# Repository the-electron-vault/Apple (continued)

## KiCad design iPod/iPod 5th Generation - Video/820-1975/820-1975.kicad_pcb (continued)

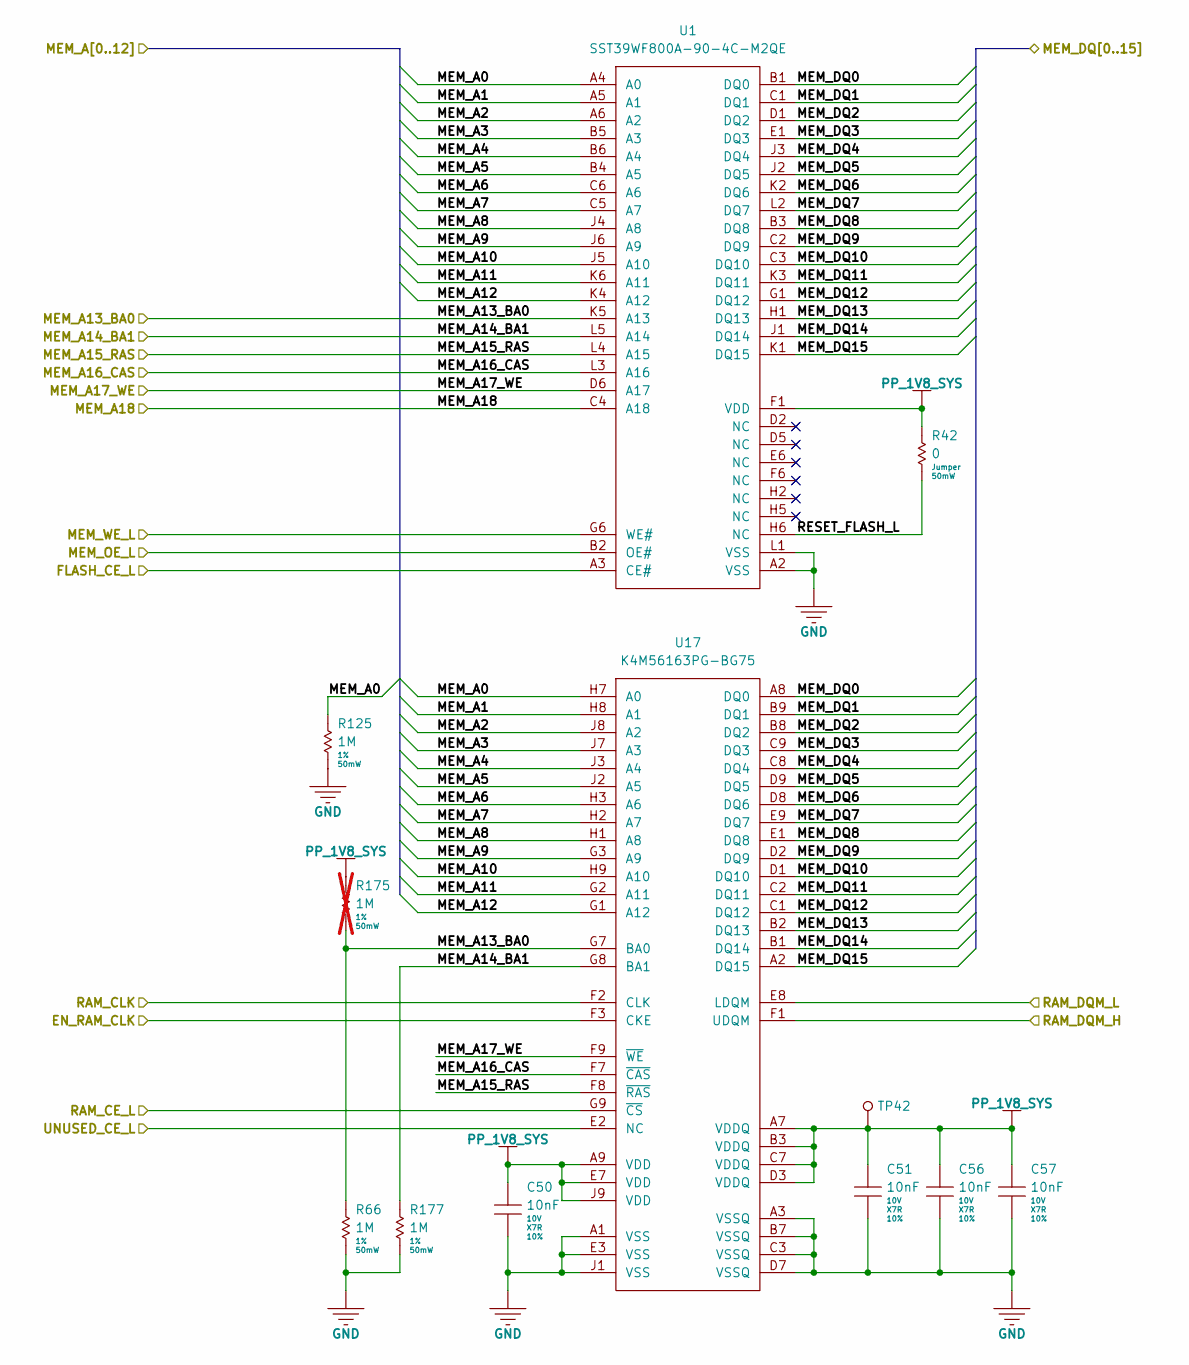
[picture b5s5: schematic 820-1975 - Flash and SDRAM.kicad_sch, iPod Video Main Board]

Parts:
C50, C51, C56, C57: 10nF; MLCC-0201; Voltage 10V; Tolerance 10%; Manufacturer Part Number GRM033R71A103KA01D
R42: 0; RES-0201; Tolerance Jumper; Manufacturer Part Number CRCW02010000Z0ED
R66, R125, R177: 1M; RES-0201; Tolerance 1%; Manufacturer Part Number CRCW02011M00FNED
R175: 1M; RES-0201; Tolerance 1%; Manufacturer Part Number CRCW02011M00FNED; not fitted
TP42: TP; TP-SMT
U1: SST39WF800A-90-4C-M2QE; Manufacturer Part Number SST39WF800A-90-4C-M2QE
U17: K4M56163PG-BG75; K4M56163PG; Manufacturer Part Number K4M56163PG-BG75

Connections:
/Flash-and-SDRAM/EN_RAM_CLK: U17.F3 (CKE); also elsewhere on the board
/Flash-and-SDRAM/FLASH_CE_L: U1.A3 (CE#); also elsewhere on the board
/Flash-and-SDRAM/MEM_A0: R125.1, U1.A4 (A0), U17.H7 (A0); also elsewhere on the board
/Flash-and-SDRAM/MEM_A1: U1.A5 (A1), U17.H8 (A1); also elsewhere on the board
/Flash-and-SDRAM/MEM_A2: U1.A6 (A2), U17.J8 (A2); also elsewhere on the board
/Flash-and-SDRAM/MEM_A3: U1.B5 (A3), U17.J7 (A3); also elsewhere on the board
/Flash-and-SDRAM/MEM_A4: U1.B6 (A4), U17.J3 (A4); also elsewhere on the board
/Flash-and-SDRAM/MEM_A5: U1.B4 (A5), U17.J2 (A5); also elsewhere on the board
/Flash-and-SDRAM/MEM_A6: U1.C6 (A6), U17.H3 (A6); also elsewhere on the board
/Flash-and-SDRAM/MEM_A7: U1.C5 (A7), U17.H2 (A7); also elsewhere on the board
/Flash-and-SDRAM/MEM_A8: U1.J4 (A8), U17.H1 (A8); also elsewhere on the board
/Flash-and-SDRAM/MEM_A9: U1.J6 (A9), U17.G3 (A9); also elsewhere on the board
/Flash-and-SDRAM/MEM_A10: U1.J5 (A10), U17.H9 (A10); also elsewhere on the board
/Flash-and-SDRAM/MEM_A11: U1.K6 (A11), U17.G2 (A11); also elsewhere on the board
/Flash-and-SDRAM/MEM_A12: U1.K4 (A12), U17.G1 (A12); also elsewhere on the board
/Flash-and-SDRAM/MEM_A13_BA0: R66.1, R175.2, U1.K5 (A13), U17.G7 (BA0); also elsewhere on the board
/Flash-and-SDRAM/MEM_A14_BA1: R177.1, U1.L5 (A14), U17.G8 (BA1); also elsewhere on the board
/Flash-and-SDRAM/MEM_A15_RAS: U1.L4 (A15), U17.F8 (~RAS); also elsewhere on the board
/Flash-and-SDRAM/MEM_A16_CAS: U1.L3 (A16), U17.F7 (~CAS); also elsewhere on the board
/Flash-and-SDRAM/MEM_A17_WE: U1.D6 (A17), U17.F9 (~WE); also elsewhere on the board
/Flash-and-SDRAM/MEM_A18: U1.C4 (A18); also elsewhere on the board
/Flash-and-SDRAM/MEM_DQ0: U1.B1 (DQ0), U17.A8 (DQ0); also elsewhere on the board
/Flash-and-SDRAM/MEM_DQ1: U1.C1 (DQ1), U17.B9 (DQ1); also elsewhere on the board
/Flash-and-SDRAM/MEM_DQ2: U1.D1 (DQ2), U17.B8 (DQ2); also elsewhere on the board
/Flash-and-SDRAM/MEM_DQ3: U1.E1 (DQ3), U17.C9 (DQ3); also elsewhere on the board
/Flash-and-SDRAM/MEM_DQ4: U1.J3 (DQ4), U17.C8 (DQ4); also elsewhere on the board
/Flash-and-SDRAM/MEM_DQ5: U1.J2 (DQ5), U17.D9 (DQ5); also elsewhere on the board
/Flash-and-SDRAM/MEM_DQ6: U1.K2 (DQ6), U17.D8 (DQ6); also elsewhere on the board
/Flash-and-SDRAM/MEM_DQ7: U1.L2 (DQ7), U17.E9 (DQ7); also elsewhere on the board
/Flash-and-SDRAM/MEM_DQ8: U1.B3 (DQ8), U17.E1 (DQ8); also elsewhere on the board
/Flash-and-SDRAM/MEM_DQ9: U1.C2 (DQ9), U17.D2 (DQ9); also elsewhere on the board
/Flash-and-SDRAM/MEM_DQ10: U1.C3 (DQ10), U17.D1 (DQ10); also elsewhere on the board
/Flash-and-SDRAM/MEM_DQ11: U1.K3 (DQ11), U17.C2 (DQ11); also elsewhere on the board
/Flash-and-SDRAM/MEM_DQ12: U1.G1 (DQ12), U17.C1 (DQ12); also elsewhere on the board
/Flash-and-SDRAM/MEM_DQ13: U1.H1 (DQ13), U17.B2 (DQ13); also elsewhere on the board
/Flash-and-SDRAM/MEM_DQ14: U1.J1 (DQ14), U17.B1 (DQ14); also elsewhere on the board
/Flash-and-SDRAM/MEM_DQ15: U1.K1 (DQ15), U17.A2 (DQ15); also elsewhere on the board
/Flash-and-SDRAM/MEM_OE_L: U1.B2 (OE#); also elsewhere on the board
/Flash-and-SDRAM/MEM_WE_L: U1.G6 (WE#); also elsewhere on the board
/Flash-and-SDRAM/RAM_CE_L: U17.G9 (~CS); also elsewhere on the board
/Flash-and-SDRAM/RAM_CLK: U17.F2 (CLK); also elsewhere on the board
/Flash-and-SDRAM/RAM_DQM_H: U17.F1 (UDQM); also elsewhere on the board
/Flash-and-SDRAM/RAM_DQM_L: U17.E8 (LDQM); also elsewhere on the board
/Flash-and-SDRAM/RESET_FLASH_L: R42.2, U1.H6 (NC)
/Flash-and-SDRAM/UNUSED_CE_L: U17.E2 (NC); also elsewhere on the board
GND: C50.2, C51.2, C56.2, C57.2, R66.2, R125.2, R177.2, U1.A2 (VSS), U1.L1 (VSS), U17.A1 (VSS), U17.A3 (VSSQ), U17.B7 (VSSQ), U17.C3 (VSSQ), U17.D7 (VSSQ), U17.E3 (VSS), U17.J1 (VSS); also elsewhere on the board
PP_1V8_SYS: C50.1, C51.1, C56.1, C57.1, R42.1, R175.1, TP42.1, U1.F1 (VDD), U17.A7 (VDDQ), U17.A9 (VDD), U17.B3 (VDDQ), U17.C7 (VDDQ), U17.D3 (VDDQ), U17.E7 (VDD), U17.J9 (VDD); also elsewhere on the board

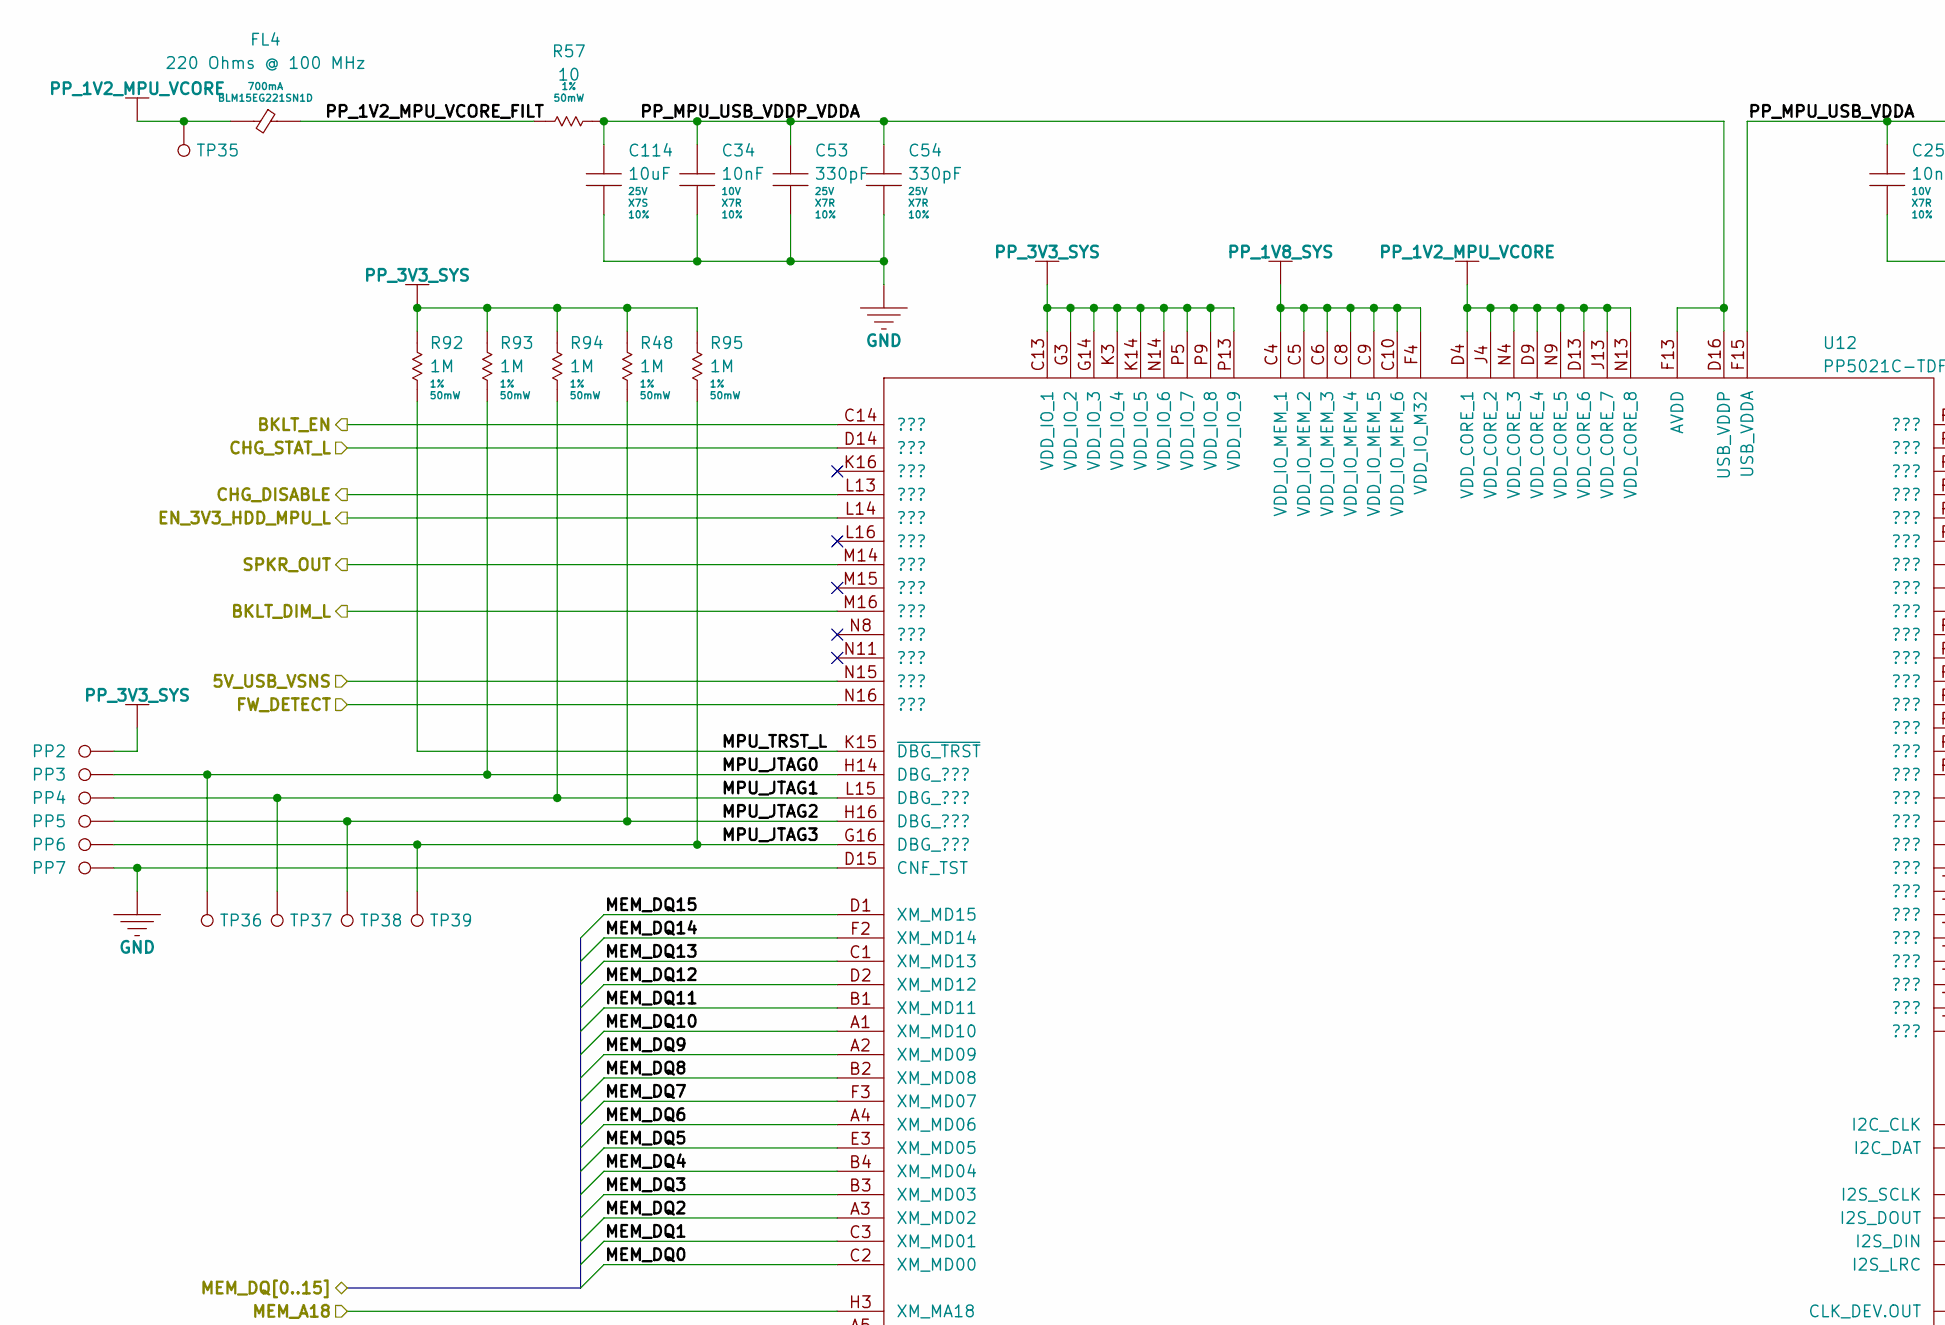
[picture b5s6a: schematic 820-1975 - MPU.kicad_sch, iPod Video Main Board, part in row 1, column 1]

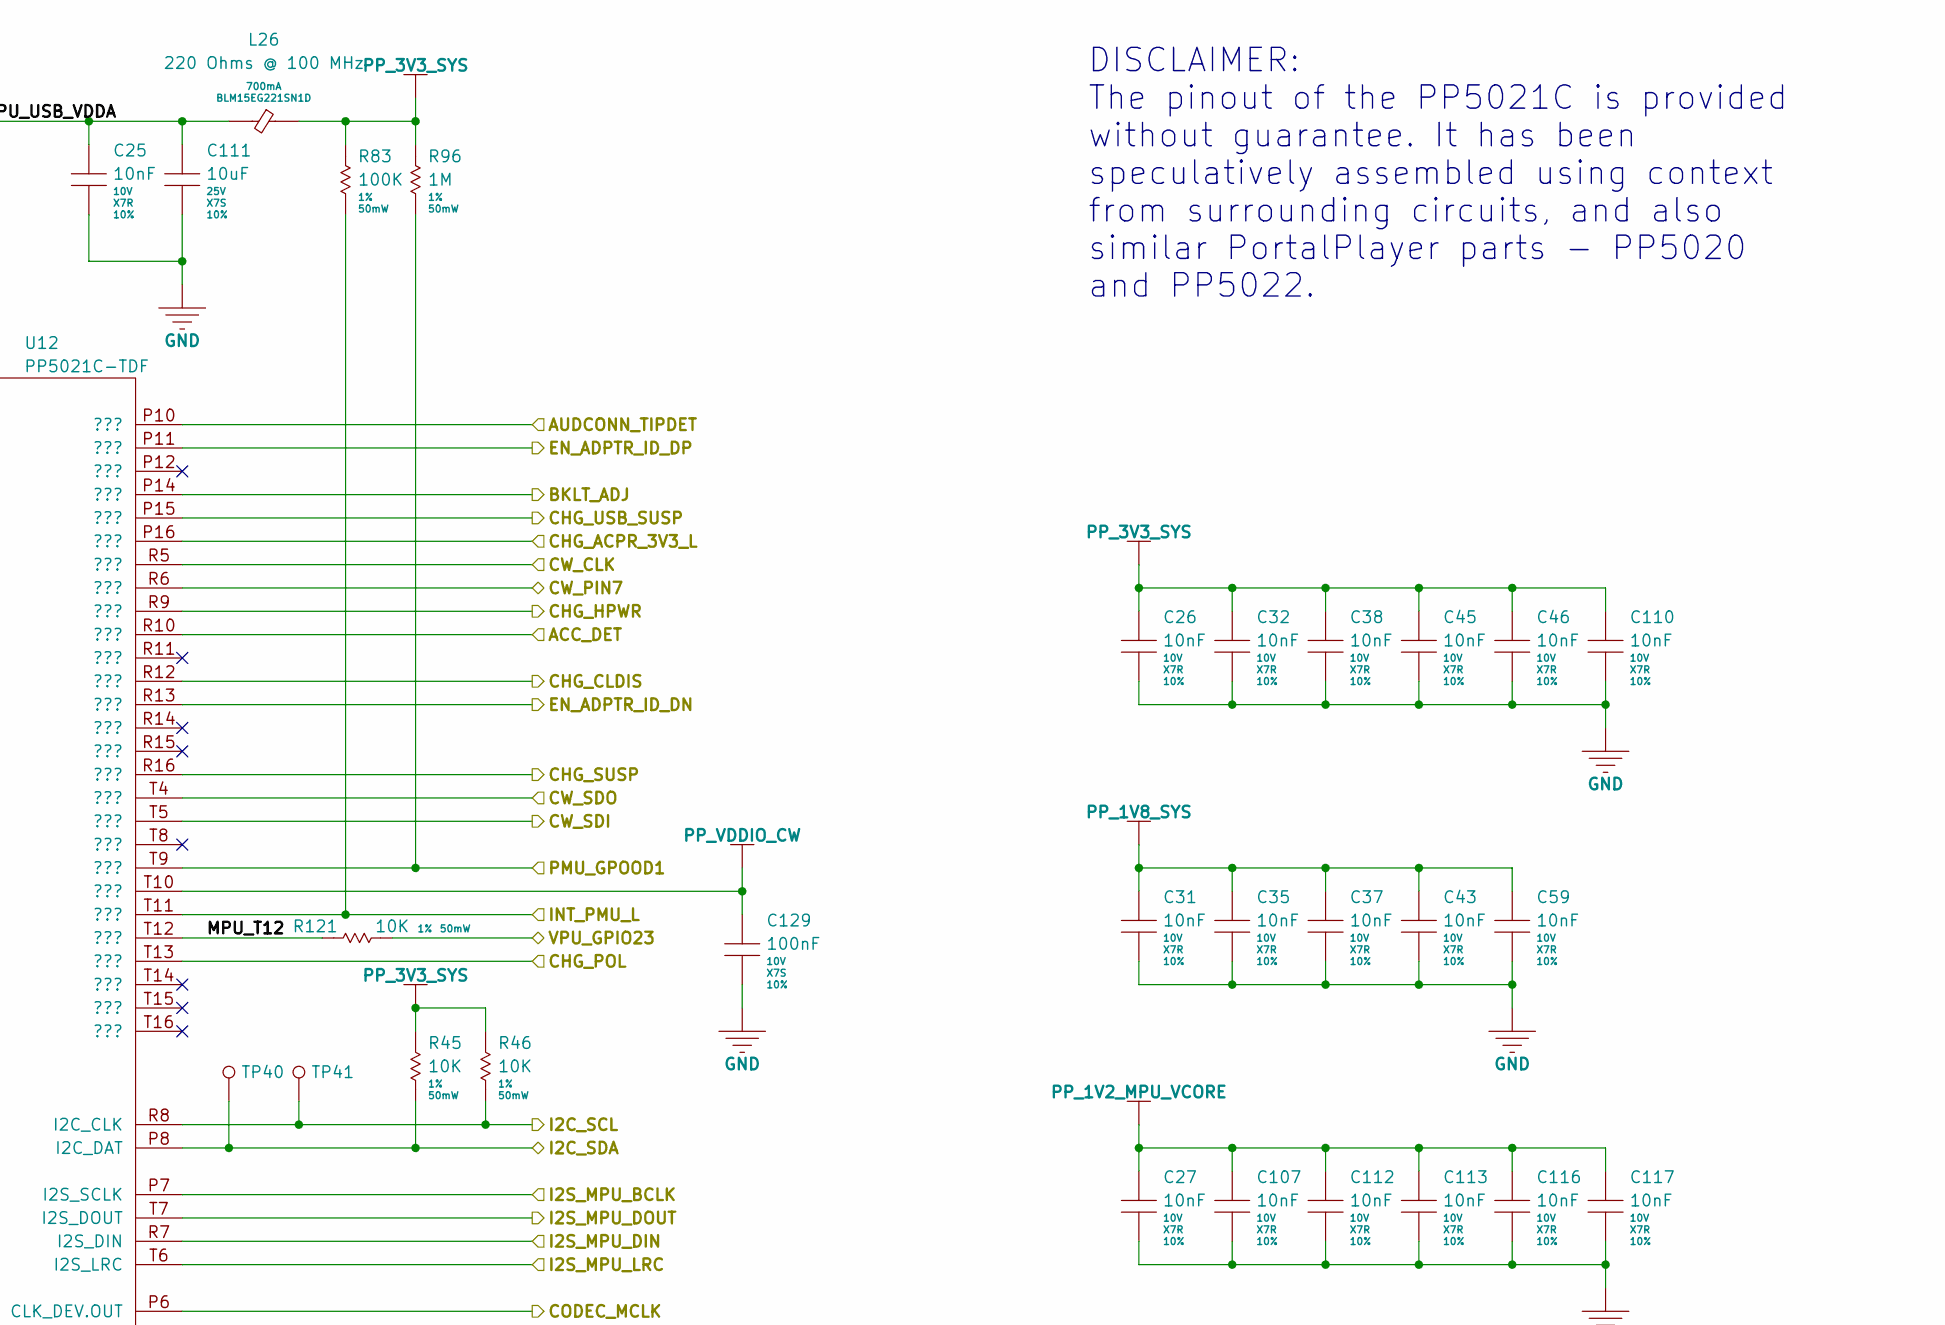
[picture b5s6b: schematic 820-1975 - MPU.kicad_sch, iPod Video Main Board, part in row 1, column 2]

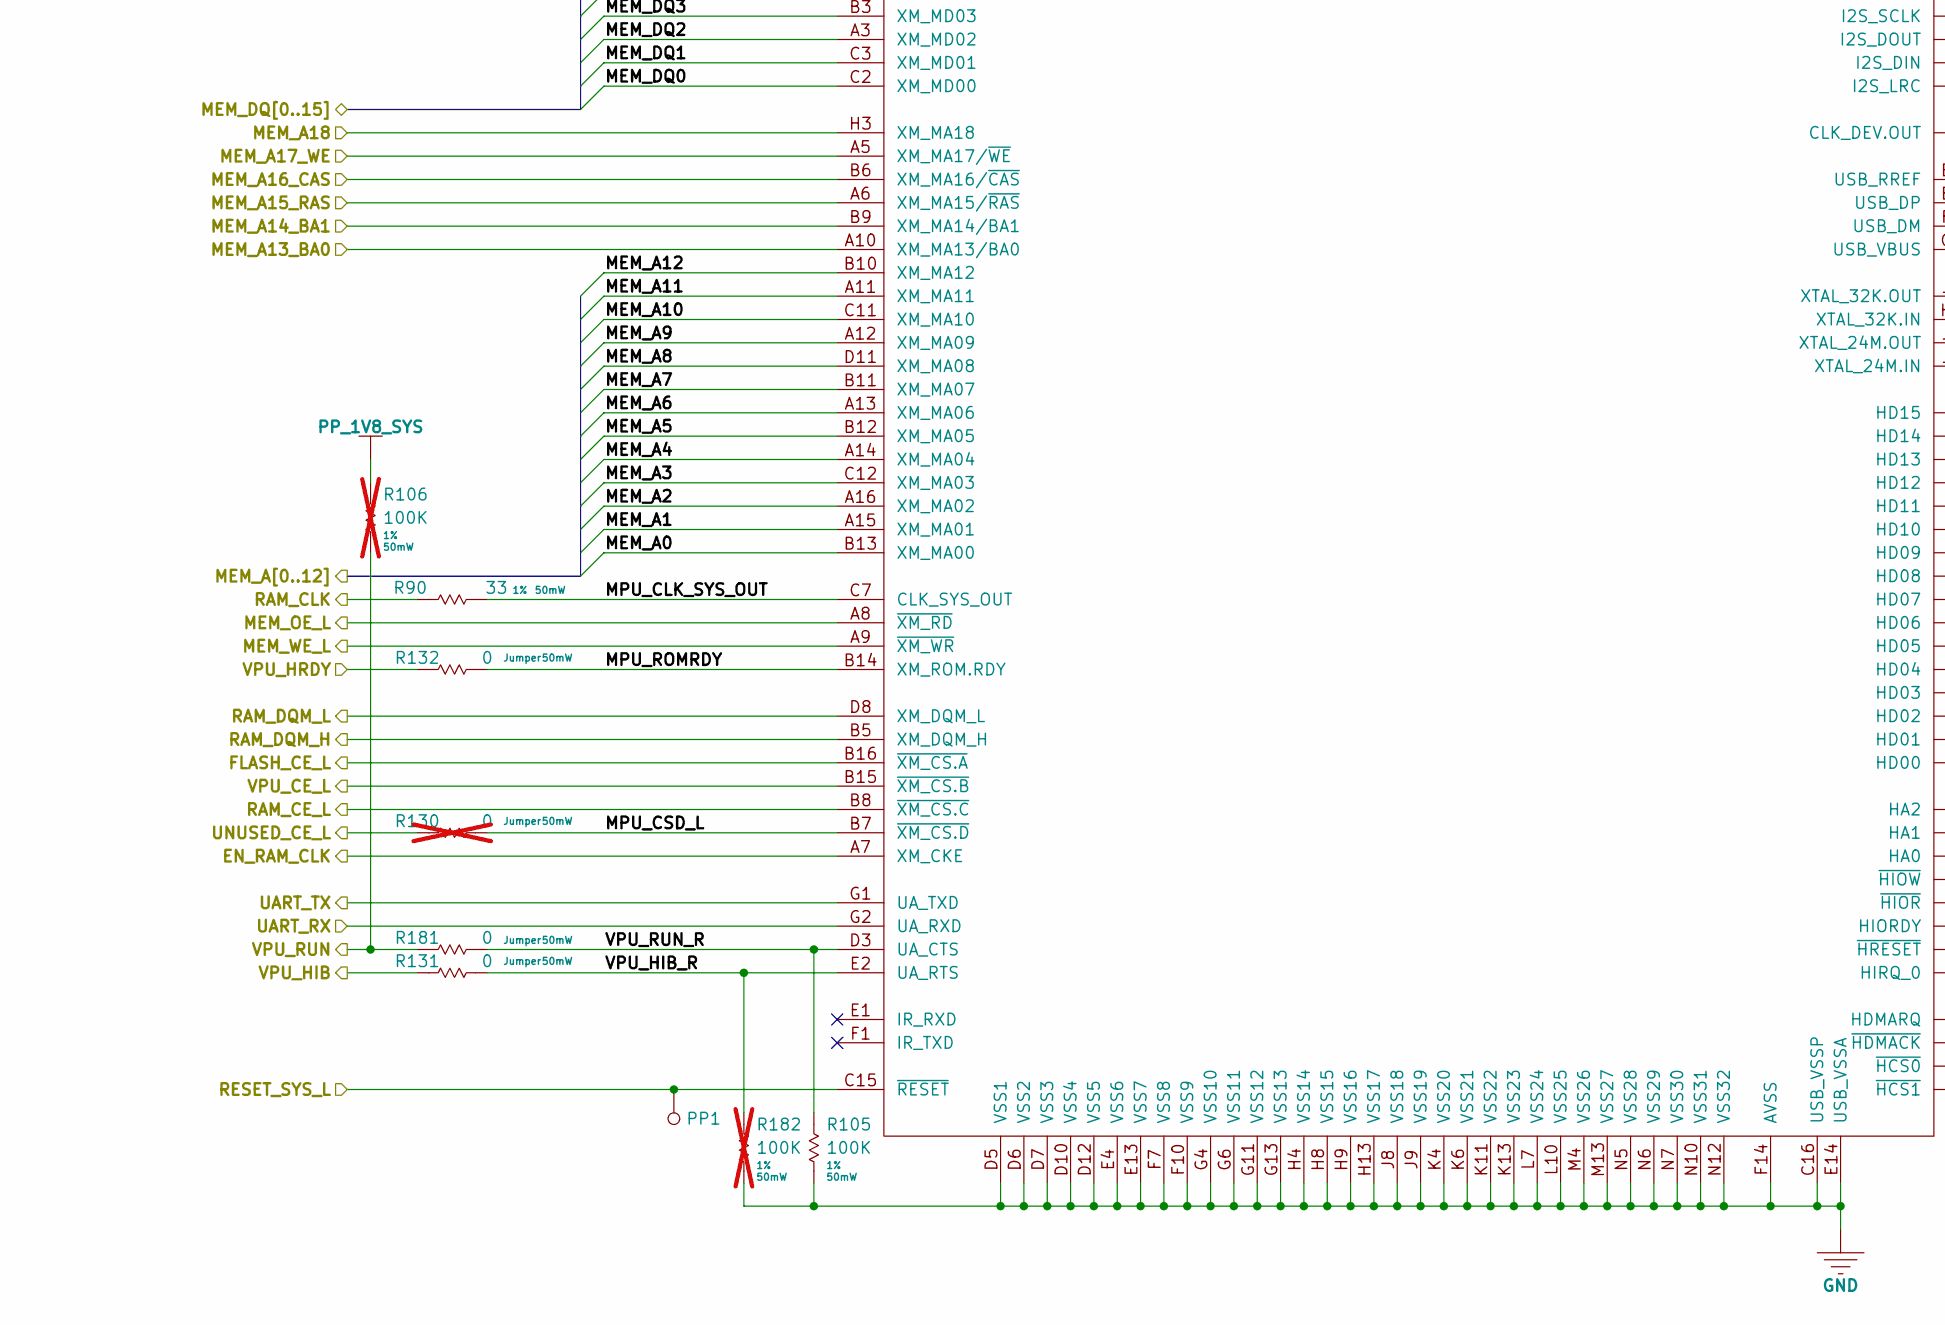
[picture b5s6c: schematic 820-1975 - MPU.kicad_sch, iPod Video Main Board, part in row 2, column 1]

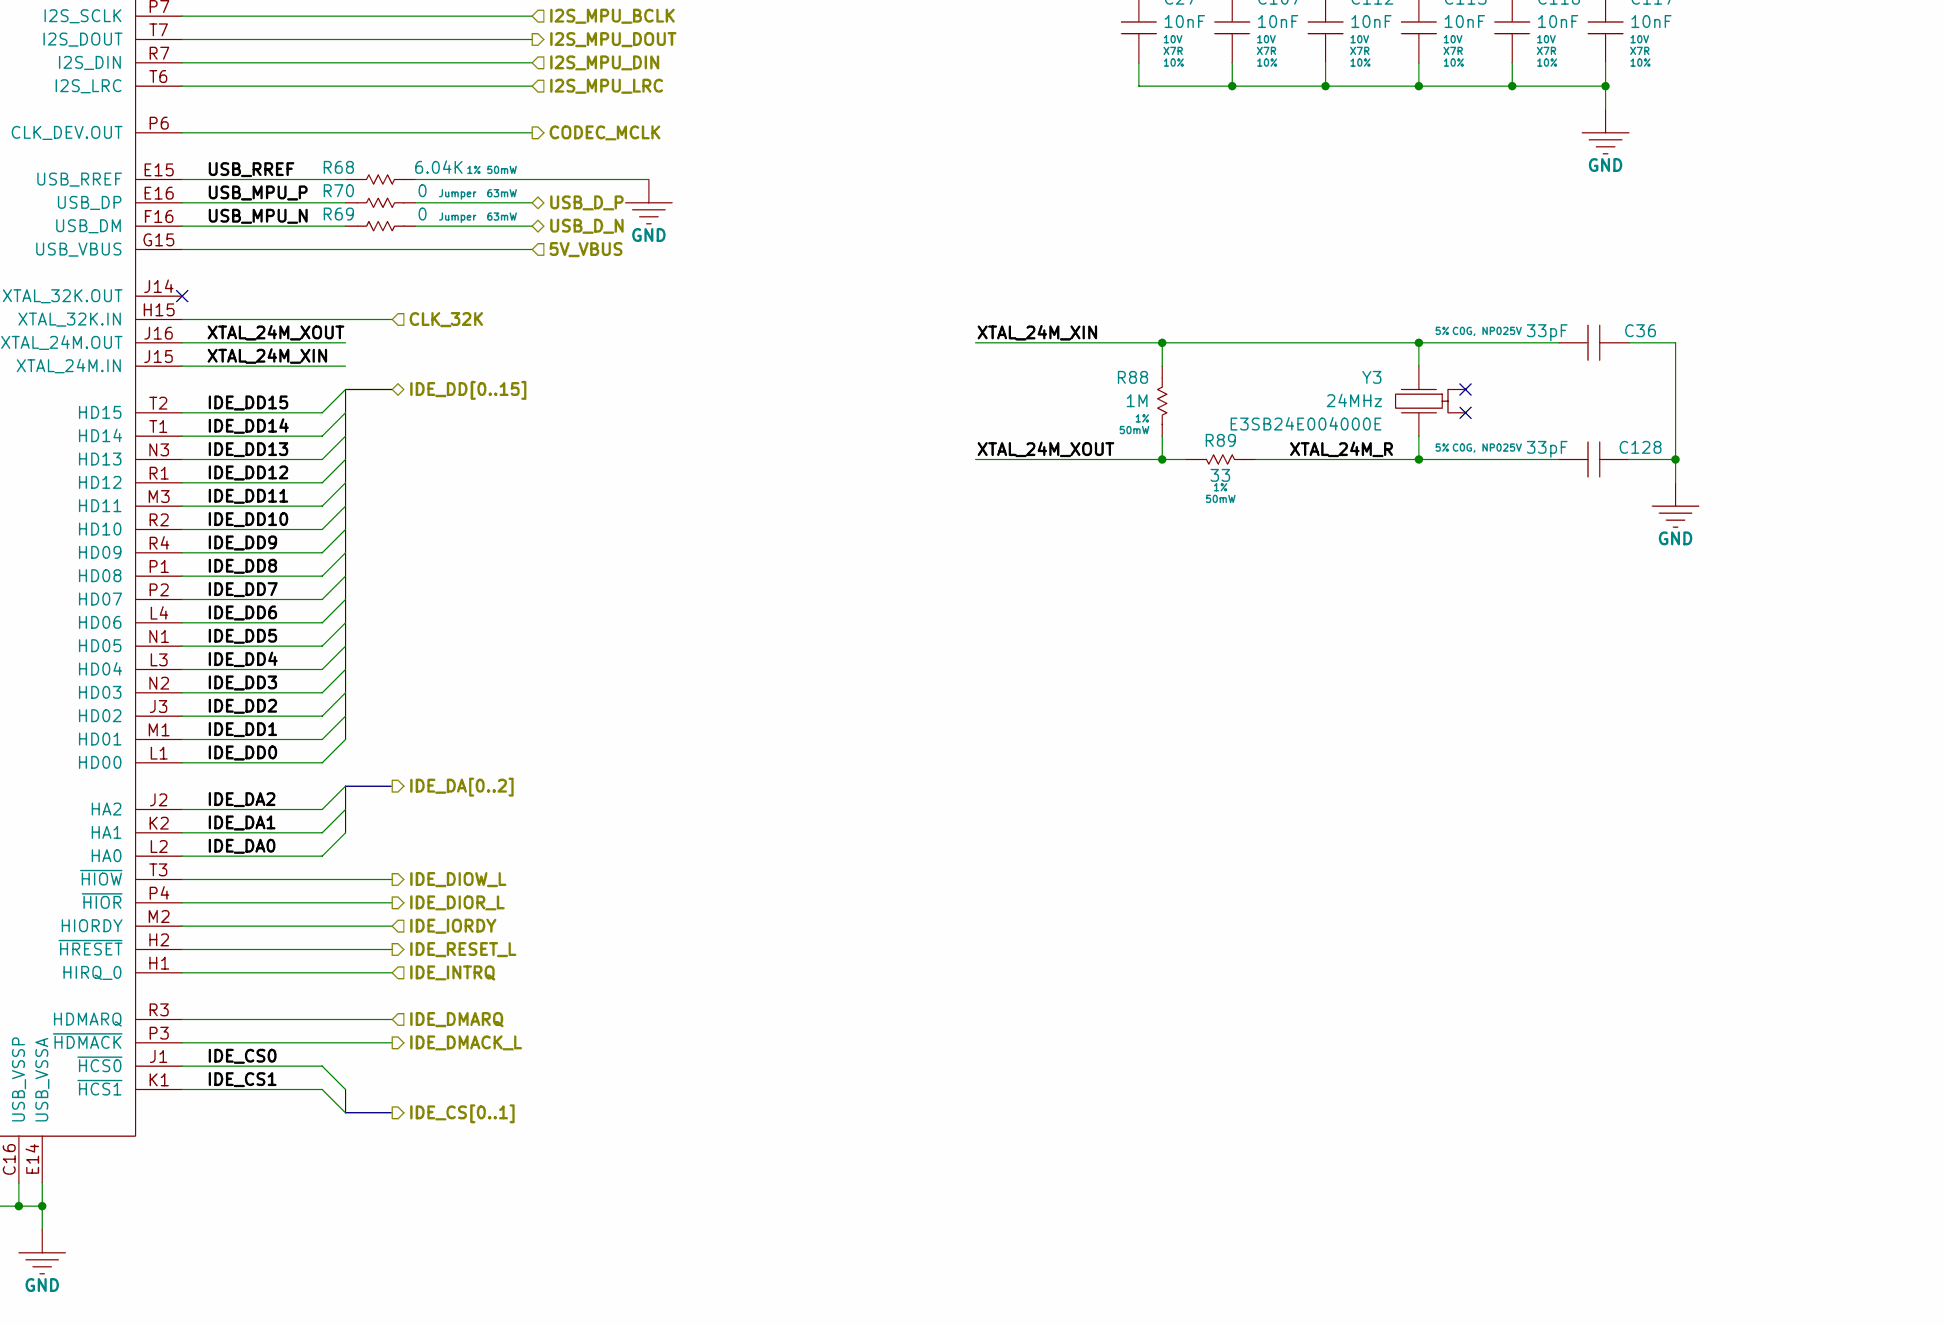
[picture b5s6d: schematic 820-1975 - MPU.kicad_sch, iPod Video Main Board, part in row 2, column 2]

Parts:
C25, C26, C27, C31, C32, C34, C35, C37, C38, C43, C45, C46, C59, C107, C110, C112, C113, C116, C117: 10nF; MLCC-0201; Voltage 10V; Tolerance 10%; Manufacturer Part Number GRM033R71A103KA01D
C36, C128: 33pF; MLCC-0201; Voltage 25V; Tolerance 5%; Manufacturer Part Number GRM0335C1E330JA01D
C53, C54: 330pF; MLCC-0201; Voltage 25V; Tolerance 10%; Manufacturer Part Number GRM033R71E331KA01D
C111, C114: 10uF; MLCC-0805; Voltage 25V; Tolerance 10%; Manufacturer Part Number GRM21BC71E106KE11L
C129: 100nF; MLCC-0201; Voltage 10V; Tolerance 10%; Manufacturer Part Number GRM033C71A104KE14D
FL4: 220 Ohms @ 100 MHz; FB-0402; Manufacturer Part Number BLM15EG221SN1D
L26: 220 Ohms @ 100 MHz; FB-0402; Manufacturer Part Number BLM15EG221SN1D
PP1, PP2, PP3, PP4, PP5, PP6, PP7: TP; TP-SMT
R45, R46, R121: 10K; RES-0201; Tolerance 1%; Manufacturer Part Number CRCW020110K0FNED
R48, R88, R92, R93, R94, R95, R96: 1M; RES-0201; Tolerance 1%; Manufacturer Part Number CRCW02011M00FNED
R57: 10; RES-0201; Tolerance 1%; Manufacturer Part Number CRCW020110R0FNED
R68: 6.04K; RES-0201; Tolerance 1%; Manufacturer Part Number CRCW02016K04FNED
R69, R70: 0; RES-0402; Tolerance Jumper; Manufacturer Part Number CRCW04020000Z0ED
R83, R105: 100K; RES-0201; Tolerance 1%; Manufacturer Part Number CRCW0201100KFNED
R89, R90: 33; RES-0201; Tolerance 1%; Manufacturer Part Number CRCW020133R0FNED
R106, R182: 100K; RES-0201; Tolerance 1%; Manufacturer Part Number CRCW0201100KFNED; not fitted
R130: 0; RES-0201; Tolerance Jumper; Manufacturer Part Number CRCW02010000Z0ED; not fitted
R131, R132, R181: 0; RES-0201; Tolerance Jumper; Manufacturer Part Number CRCW02010000Z0ED
TP35, TP36, TP37, TP38, TP39, TP40, TP41: TP; TP-SMT
U12: PP5021C-TDF; Manufacturer Part Number PP5021C-TDF
Y3: 24MHz; XTAL-3.2x2.5; Tolerance 10ppm; Manufacturer Part Number E3SB24E004000E

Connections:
/BKLT_ADJ: U12.P14 (???); also elsewhere on the board
/BKLT_DIM_L: U12.M16 (???); also elsewhere on the board
/BKLT_EN: U12.C14 (???); also elsewhere on the board
/CODEC/AUDCONN_TIPDET: U12.P10 (???); also elsewhere on the board
/CODEC/CODEC_MCLK: U12.P6 (CLK_DEV.OUT); also elsewhere on the board
/CODEC/I2C_SCL: R46.2, TP41.1, U12.R8 (I2C_CLK); also elsewhere on the board
/CODEC/I2C_SDA: R45.2, TP40.1, U12.P8 (I2C_DAT); also elsewhere on the board
/CODEC/I2S_MPU_BCLK: U12.P7 (I2S_SCLK); also elsewhere on the board
/CODEC/I2S_MPU_DIN: U12.R7 (I2S_DIN); also elsewhere on the board
/CODEC/I2S_MPU_DOUT: U12.T7 (I2S_DOUT); also elsewhere on the board
/CODEC/I2S_MPU_LRC: U12.T6 (I2S_LRC); also elsewhere on the board
/CODEC/SPKR_OUT: U12.M14 (???); also elsewhere on the board
/Charger-and-3.3V-Supply/CHG_ACPR_3V3_L: U12.P16 (???); also elsewhere on the board
/Charger-and-3.3V-Supply/CHG_CLDIS: U12.R12 (???); also elsewhere on the board
/Charger-and-3.3V-Supply/CHG_DISABLE: U12.L13 (???); also elsewhere on the board
/Charger-and-3.3V-Supply/CHG_HPWR: U12.R9 (???); also elsewhere on the board
/Charger-and-3.3V-Supply/CHG_POL: U12.T13 (???); also elsewhere on the board
/Charger-and-3.3V-Supply/CHG_STAT_L: U12.D14 (???); also elsewhere on the board
/Charger-and-3.3V-Supply/CHG_SUSP: U12.R16 (???); also elsewhere on the board
/Charger-and-3.3V-Supply/CHG_USB_SUSP: U12.P15 (???); also elsewhere on the board
/Click-Wheel/CW_CLK: U12.R5 (???); also elsewhere on the board
/Click-Wheel/CW_PIN7: U12.R6 (???); also elsewhere on the board
/Click-Wheel/CW_SDI: U12.T5 (???); also elsewhere on the board
/Click-Wheel/CW_SDO: U12.T4 (???); also elsewhere on the board
/Dock-Interface/5V_USB_VSNS: U12.N15 (???); also elsewhere on the board
/Dock-Interface/5V_VBUS: U12.G15 (USB_VBUS); also elsewhere on the board
/Dock-Interface/EN_ADPTR_ID_DN: U12.R13 (???); also elsewhere on the board
/Dock-Interface/EN_ADPTR_ID_DP: U12.P11 (???); also elsewhere on the board
/Dock-Interface/FW_DETECT: U12.N16 (???); also elsewhere on the board
/Dock-Interface/UART_RX: U12.G2 (UA_RXD); also elsewhere on the board
/Dock-Interface/UART_TX: U12.G1 (UA_TXD); also elsewhere on the board
/Dock-Interface/USB_D_N: R69.2; also elsewhere on the board
/Dock-Interface/USB_D_P: R70.2; also elsewhere on the board
/Flash-and-SDRAM/EN_RAM_CLK: U12.A7 (XM_CKE); also elsewhere on the board
/Flash-and-SDRAM/FLASH_CE_L: U12.B16 (~XM_CS.A); also elsewhere on the board
/Flash-and-SDRAM/MEM_A0: U12.B13 (XM_MA00); also elsewhere on the board
/Flash-and-SDRAM/MEM_A1: U12.A15 (XM_MA01); also elsewhere on the board
/Flash-and-SDRAM/MEM_A2: U12.A16 (XM_MA02); also elsewhere on the board
/Flash-and-SDRAM/MEM_A3: U12.C12 (XM_MA03); also elsewhere on the board
/Flash-and-SDRAM/MEM_A4: U12.A14 (XM_MA04); also elsewhere on the board
/Flash-and-SDRAM/MEM_A5: U12.B12 (XM_MA05); also elsewhere on the board
/Flash-and-SDRAM/MEM_A6: U12.A13 (XM_MA06); also elsewhere on the board
/Flash-and-SDRAM/MEM_A7: U12.B11 (XM_MA07); also elsewhere on the board
/Flash-and-SDRAM/MEM_A8: U12.D11 (XM_MA08); also elsewhere on the board
/Flash-and-SDRAM/MEM_A9: U12.A12 (XM_MA09); also elsewhere on the board
/Flash-and-SDRAM/MEM_A10: U12.C11 (XM_MA10); also elsewhere on the board
/Flash-and-SDRAM/MEM_A11: U12.A11 (XM_MA11); also elsewhere on the board
/Flash-and-SDRAM/MEM_A12: U12.B10 (XM_MA12); also elsewhere on the board
/Flash-and-SDRAM/MEM_A13_BA0: U12.A10 (XM_MA13/BA0); also elsewhere on the board
/Flash-and-SDRAM/MEM_A14_BA1: U12.B9 (XM_MA14/BA1); also elsewhere on the board
/Flash-and-SDRAM/MEM_A15_RAS: U12.A6 (XM_MA15/~RAS); also elsewhere on the board
/Flash-and-SDRAM/MEM_A16_CAS: U12.B6 (XM_MA16/~CAS); also elsewhere on the board
/Flash-and-SDRAM/MEM_A17_WE: U12.A5 (XM_MA17/~WE); also elsewhere on the board
/Flash-and-SDRAM/MEM_A18: U12.H3 (XM_MA18); also elsewhere on the board
/Flash-and-SDRAM/MEM_DQ0: U12.C2 (XM_MD00); also elsewhere on the board
/Flash-and-SDRAM/MEM_DQ1: U12.C3 (XM_MD01); also elsewhere on the board
/Flash-and-SDRAM/MEM_DQ2: U12.A3 (XM_MD02); also elsewhere on the board
/Flash-and-SDRAM/MEM_DQ3: U12.B3 (XM_MD03); also elsewhere on the board
/Flash-and-SDRAM/MEM_DQ4: U12.B4 (XM_MD04); also elsewhere on the board
/Flash-and-SDRAM/MEM_DQ5: U12.E3 (XM_MD05); also elsewhere on the board
/Flash-and-SDRAM/MEM_DQ6: U12.A4 (XM_MD06); also elsewhere on the board
/Flash-and-SDRAM/MEM_DQ7: U12.F3 (XM_MD07); also elsewhere on the board
/Flash-and-SDRAM/MEM_DQ8: U12.B2 (XM_MD08); also elsewhere on the board
/Flash-and-SDRAM/MEM_DQ9: U12.A2 (XM_MD09); also elsewhere on the board
/Flash-and-SDRAM/MEM_DQ10: U12.A1 (XM_MD10); also elsewhere on the board
/Flash-and-SDRAM/MEM_DQ11: U12.B1 (XM_MD11); also elsewhere on the board
/Flash-and-SDRAM/MEM_DQ12: U12.D2 (XM_MD12); also elsewhere on the board
/Flash-and-SDRAM/MEM_DQ13: U12.C1 (XM_MD13); also elsewhere on the board
/Flash-and-SDRAM/MEM_DQ14: U12.F2 (XM_MD14); also elsewhere on the board
/Flash-and-SDRAM/MEM_DQ15: U12.D1 (XM_MD15); also elsewhere on the board
/Flash-and-SDRAM/MEM_OE_L: U12.A8 (~XM_RD); also elsewhere on the board
/Flash-and-SDRAM/MEM_WE_L: U12.A9 (~XM_WR); also elsewhere on the board
/Flash-and-SDRAM/RAM_CE_L: U12.B8 (~XM_CS.C); also elsewhere on the board
/Flash-and-SDRAM/RAM_CLK: R90.1; also elsewhere on the board
/Flash-and-SDRAM/RAM_DQM_H: U12.B5 (XM_DQM_H); also elsewhere on the board
/Flash-and-SDRAM/RAM_DQM_L: U12.D8 (XM_DQM_L); also elsewhere on the board
/Flash-and-SDRAM/UNUSED_CE_L: R130.1; also elsewhere on the board
/Hard-Disk/EN_3V3_HDD_MPU_L: U12.L14 (???); also elsewhere on the board
/Hard-Disk/IDE_CS0: U12.J1 (~HCS0); also elsewhere on the board
/Hard-Disk/IDE_CS1: U12.K1 (~HCS1); also elsewhere on the board
/Hard-Disk/IDE_DA0: U12.L2 (HA0); also elsewhere on the board
/Hard-Disk/IDE_DA1: U12.K2 (HA1); also elsewhere on the board
/Hard-Disk/IDE_DA2: U12.J2 (HA2); also elsewhere on the board
/Hard-Disk/IDE_DD0: U12.L1 (HD00); also elsewhere on the board
/Hard-Disk/IDE_DD1: U12.M1 (HD01); also elsewhere on the board
/Hard-Disk/IDE_DD2: U12.J3 (HD02); also elsewhere on the board
/Hard-Disk/IDE_DD3: U12.N2 (HD03); also elsewhere on the board
/Hard-Disk/IDE_DD4: U12.L3 (HD04); also elsewhere on the board
/Hard-Disk/IDE_DD5: U12.N1 (HD05); also elsewhere on the board
/Hard-Disk/IDE_DD6: U12.L4 (HD06); also elsewhere on the board
/Hard-Disk/IDE_DD7: U12.P2 (HD07); also elsewhere on the board
/Hard-Disk/IDE_DD8: U12.P1 (HD08); also elsewhere on the board
/Hard-Disk/IDE_DD9: U12.R4 (HD09); also elsewhere on the board
/Hard-Disk/IDE_DD10: U12.R2 (HD10); also elsewhere on the board
/Hard-Disk/IDE_DD11: U12.M3 (HD11); also elsewhere on the board
/Hard-Disk/IDE_DD12: U12.R1 (HD12); also elsewhere on the board
/Hard-Disk/IDE_DD13: U12.N3 (HD13); also elsewhere on the board
/Hard-Disk/IDE_DD14: U12.T1 (HD14); also elsewhere on the board
/Hard-Disk/IDE_DD15: U12.T2 (HD15); also elsewhere on the board
/Hard-Disk/IDE_DIOR_L: U12.P4 (~HIOR); also elsewhere on the board
/Hard-Disk/IDE_DIOW_L: U12.T3 (~HIOW); also elsewhere on the board
/Hard-Disk/IDE_DMACK_L: U12.P3 (~HDMACK); also elsewhere on the board
/Hard-Disk/IDE_DMARQ: U12.R3 (HDMARQ); also elsewhere on the board
/Hard-Disk/IDE_INTRQ: U12.H1 (HIRQ_0); also elsewhere on the board
/Hard-Disk/IDE_IORDY: U12.M2 (HIORDY); also elsewhere on the board
/Hard-Disk/IDE_RESET_L: U12.H2 (~HRESET); also elsewhere on the board
/Hard-Disk/RESET_SYS_L: PP1.1, U12.C15 (~RESET); also elsewhere on the board
/MPU/ACC_DET: U12.R10 (???); also elsewhere on the board
/MPU/CLK_32K: U12.H15 (XTAL_32K.IN); also elsewhere on the board
/MPU/INT_PMU_L: R83.2, U12.T11 (???); also elsewhere on the board
/MPU/MPU_CLK_SYS_OUT: R90.2, U12.C7 (CLK_SYS_OUT)
/MPU/MPU_CSD_L: R130.2, U12.B7 (~XM_CS.D)
/MPU/MPU_JTAG0: PP3.1, R93.2, TP36.1, U12.H14 (DBG_???)
/MPU/MPU_JTAG1: PP4.1, R94.2, TP37.1, U12.L15 (DBG_???)
/MPU/MPU_JTAG2: PP5.1, R48.2, TP38.1, U12.H16 (DBG_???)
/MPU/MPU_JTAG3: PP6.1, R95.2, TP39.1, U12.G16 (DBG_???)
/MPU/MPU_ROMRDY: R132.2, U12.B14 (XM_ROM.RDY)
/MPU/MPU_T12: R121.1, U12.T12 (???)
/MPU/MPU_TRST_L: R92.2, U12.K15 (~DBG_TRST)
/MPU/PMU_GPOOD1: R96.2, U12.T9 (???); also elsewhere on the board
/MPU/PP_1V2_MPU_VCORE_FILT: FL4.2, R57.1
/MPU/PP_MPU_USB_VDDA: C25.1, C111.1, L26.1, U12.F15 (USB_VDDA)
/MPU/PP_MPU_USB_VDDP_VDDA: C34.1, C53.1, C54.1, C114.1, R57.2, U12.D16 (USB_VDDP), U12.F13 (AVDD)
/MPU/USB_MPU_N: R69.1, U12.F16 (USB_DM)
/MPU/USB_MPU_P: R70.1, U12.E16 (USB_DP)
/MPU/USB_RREF: R68.1, U12.E15 (USB_RREF)
/MPU/VPU_CE_L: U12.B15 (~XM_CS.B); also elsewhere on the board
/MPU/VPU_GPIO23: R121.2; also elsewhere on the board
/MPU/VPU_HIB: R131.1; also elsewhere on the board
/MPU/VPU_HIB_R: R131.2, R182.1, U12.E2 (UA_RTS)
/MPU/VPU_HRDY: R132.1; also elsewhere on the board
/MPU/VPU_RUN: R106.2, R181.1; also elsewhere on the board
/MPU/VPU_RUN_R: R105.1, R181.2, U12.D3 (UA_CTS)
/MPU/XTAL_24M_R: C128.1, R89.1, Y3.3
/MPU/XTAL_24M_XIN: C36.1, R88.1, U12.J15 (XTAL_24M.IN), Y3.1
/MPU/XTAL_24M_XOUT: R88.2, R89.2, U12.J16 (XTAL_24M.OUT)
GND: C25.2, C26.2, C27.2, C31.2, C32.2, C34.2, C35.2, C36.2, C37.2, C38.2, C43.2, C45.2, C46.2, C53.2, C54.2, C59.2, C107.2, C110.2, C111.2, C112.2, C113.2, C114.2, C116.2, C117.2, C128.2, C129.2, PP7.1, R68.2, R105.2, R182.2, U12.C16 (USB_VSSP), U12.D5 (VSS1), U12.D6 (VSS2), U12.D7 (VSS3), U12.D10 (VSS4), U12.D12 (VSS5), U12.D15 (CNF_TST), U12.E4 (VSS6), U12.E13 (VSS7), U12.E14 (USB_VSSA), U12.F7 (VSS8), U12.F10 (VSS9), U12.F14 (AVSS), U12.G4 (VSS10), U12.G6 (VSS11), U12.G11 (VSS12), U12.G13 (VSS13), U12.H4 (VSS14), U12.H8 (VSS15), U12.H9 (VSS16), U12.H13 (VSS17), U12.J8 (VSS18), U12.J9 (VSS19), U12.K4 (VSS20), U12.K6 (VSS21), U12.K11 (VSS22), U12.K13 (VSS23), U12.L7 (VSS24), U12.L10 (VSS25), U12.M4 (VSS26), U12.M13 (VSS27), U12.N5 (VSS28), U12.N6 (VSS29), U12.N7 (VSS30), U12.N10 (VSS31), U12.N12 (VSS32); also elsewhere on the board
PP_1V2_MPU_VCORE: C27.1, C107.1, C112.1, C113.1, C116.1, C117.1, FL4.1, TP35.1, U12.D4 (VDD_CORE_1), U12.D9 (VDD_CORE_4), U12.D13 (VDD_CORE_6), U12.J4 (VDD_CORE_2), U12.J13 (VDD_CORE_7), U12.N4 (VDD_CORE_3), U12.N9 (VDD_CORE_5), U12.N13 (VDD_CORE_8); also elsewhere on the board
PP_1V8_SYS: C31.1, C35.1, C37.1, C43.1, C59.1, R106.1, U12.C4 (VDD_IO_MEM_1), U12.C5 (VDD_IO_MEM_2), U12.C6 (VDD_IO_MEM_3), U12.C8 (VDD_IO_MEM_4), U12.C9 (VDD_IO_MEM_5), U12.C10 (VDD_IO_MEM_6), U12.F4 (VDD_IO_M32); also elsewhere on the board
PP_3V3_SYS: C26.1, C32.1, C38.1, C45.1, C46.1, C110.1, L26.2, PP2.1, R45.1, R46.1, R48.1, R83.1, R92.1, R93.1, R94.1, R95.1, R96.1, U12.C13 (VDD_IO_1), U12.G3 (VDD_IO_2), U12.G14 (VDD_IO_3), U12.K3 (VDD_IO_4), U12.K14 (VDD_IO_5), U12.N14 (VDD_IO_6), U12.P5 (VDD_IO_7), U12.P9 (VDD_IO_8), U12.P13 (VDD_IO_9); also elsewhere on the board
PP_VDDIO_CW: C129.1, U12.T10 (???); also elsewhere on the board

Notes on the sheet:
DISCLAIMER: The pinout of the PP5021C is provided without guarantee. It has been speculatively assembled using context from surrounding circuits, and also similar PortalPlayer parts - PP5020 and PP5022.
